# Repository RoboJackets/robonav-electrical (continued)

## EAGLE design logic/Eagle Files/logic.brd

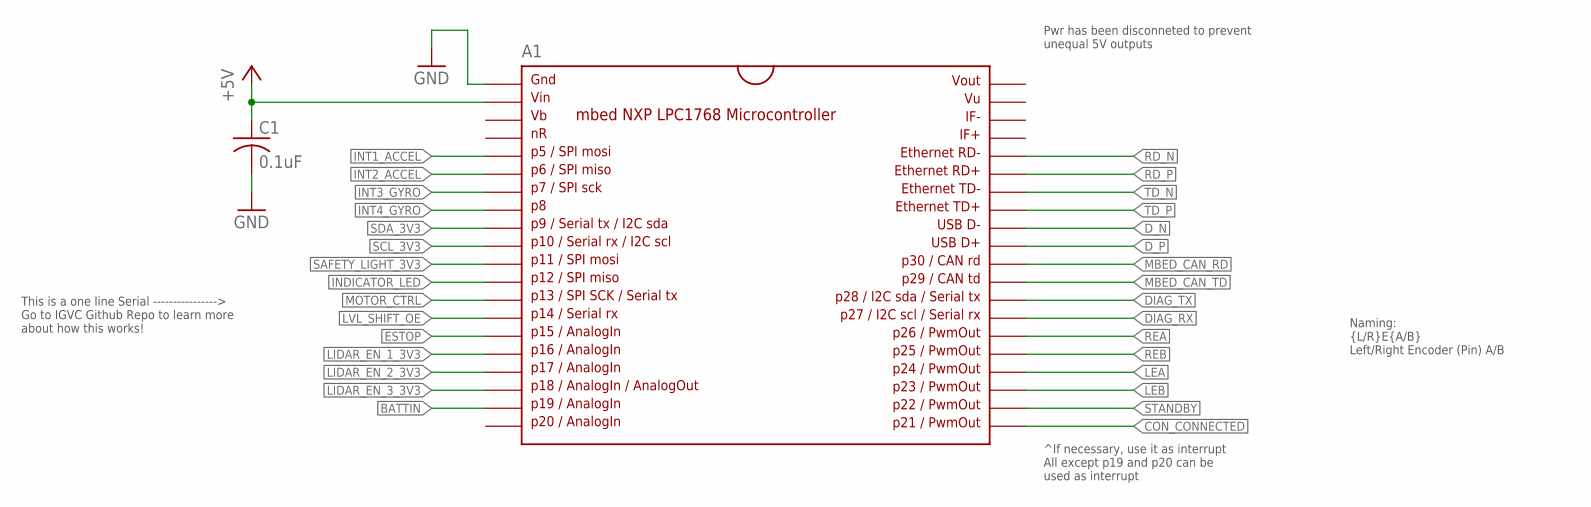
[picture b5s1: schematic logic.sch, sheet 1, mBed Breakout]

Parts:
A1: MBED1768; SPARKFUN-BOARDS_DIL40_0.9
C1: 0.1uF; C0603

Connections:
+5V: A1.2, C1.1; also elsewhere on the board
BATTIN: A1.19; also elsewhere on the board
CON_CONNECTED: A1.21; also elsewhere on the board
DIAG_RX: A1.27; also elsewhere on the board
DIAG_TX: A1.28; also elsewhere on the board
D_N: A1.32; also elsewhere on the board
D_P: A1.31; also elsewhere on the board
ESTOP: A1.15; also elsewhere on the board
GND: A1.1, C1.2; also elsewhere on the board
INDICATOR_LED: A1.12; also elsewhere on the board
INT1_ACCEL: A1.5; also elsewhere on the board
INT2_ACCEL: A1.6; also elsewhere on the board
INT3_GYRO: A1.7; also elsewhere on the board
INT4_GYRO: A1.8; also elsewhere on the board
LEA: A1.24; also elsewhere on the board
LEB: A1.23; also elsewhere on the board
LIDAR_EN_1_3V3: A1.16; also elsewhere on the board
LIDAR_EN_2_3V3: A1.17; also elsewhere on the board
LIDAR_EN_3_3V3: A1.18; also elsewhere on the board
LVL_SHIFT_OE: A1.14; also elsewhere on the board
MBED_CAN_RD: A1.30; also elsewhere on the board
MBED_CAN_TD: A1.29; also elsewhere on the board
MOTOR_CTRL: A1.13; also elsewhere on the board
RD_N: A1.36; also elsewhere on the board
RD_P: A1.35; also elsewhere on the board
REA: A1.26; also elsewhere on the board
REB: A1.25; also elsewhere on the board
SAFETY_LIGHT_3V3: A1.11; also elsewhere on the board
SCL_3V3: A1.10; also elsewhere on the board
SDA_3V3: A1.9; also elsewhere on the board
STANDBY: A1.22; also elsewhere on the board
TD_N: A1.34; also elsewhere on the board
TD_P: A1.33; also elsewhere on the board

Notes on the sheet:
Naming: {L/R}E{A/B} Left/Right Encoder (Pin) A/B
This is a one line Serial ----------------> Go to IGVC Github Repo to learn more about how this works!
^If necessary, use it as interrupt All except p19 and p20 can be used as interrupt
Pwr has been disconneted to prevent unequal 5V outputs

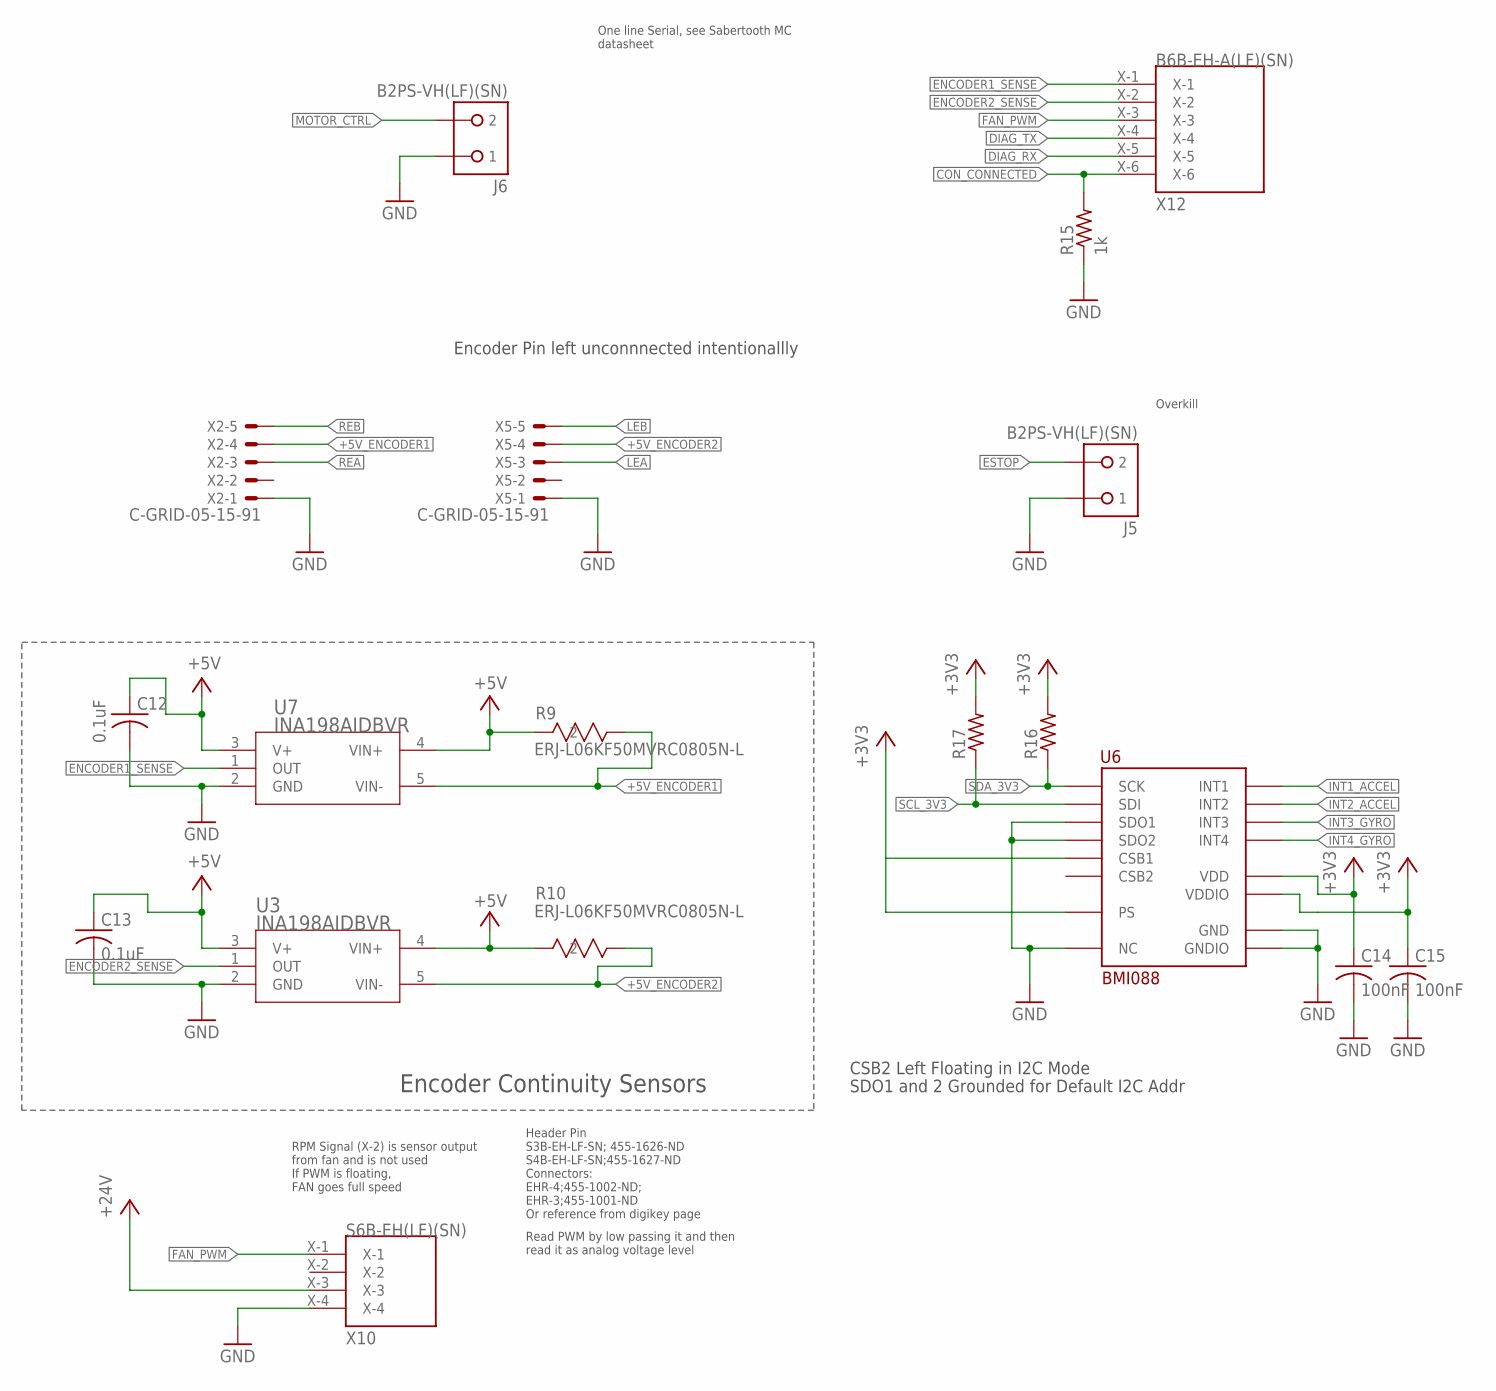
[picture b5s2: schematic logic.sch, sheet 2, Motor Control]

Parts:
C12, C13: 0.1uF; C0603
C14, C15: 100nF; C0603
J5, J6: B2PS-VH(LF)(SN); B2PS-CENTERED
R9, R10: ERJ-L06KF50MVRC0805N-L; RC0805N-L
R15: 1k; R0603
R16, R17: R-US_R0603; R0603
U3, U7: INA198AIDBVR; DBV5
U6: BMI088
X2, X5: C-GRID-05-15-91; 15-91-05
X10: S6B-EH(LF)(SN); S4BEHLFSN
X12: B6B-EH-A(LF)(SN); B6BEHALFSN

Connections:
+3V3: C14.1, C15.1, R16.2, R17.2, U6.P$3 (VDD), U6.P$7 (PS), U6.P$11 (VDDIO); also elsewhere on the board
+5V: C12.1, C13.1, R9.2, R10.2, U3.3 (V+), U3.4 (VIN+), U7.3 (V+), U7.4 (VIN+); also elsewhere on the board
+5V_ENCODER1: R9.1, U7.5 (VIN-), X2.4
+5V_ENCODER2: R10.1, U3.5 (VIN-), X5.4
+24V: X10.X-3; also elsewhere on the board
CON_CONNECTED: R15.2, X12.X-6; also elsewhere on the board
DIAG_RX: X12.X-5; also elsewhere on the board
DIAG_TX: X12.X-4; also elsewhere on the board
ENCODER1_SENSE: U7.1 (OUT), X12.X-1
ENCODER2_SENSE: U3.1 (OUT), X12.X-2
ESTOP: J5.2; also elsewhere on the board
FAN_PWM: X10.X-1, X12.X-3
GND: C12.2, C13.2, C14.2, C15.2, J5.1, J6.1, R15.1, U3.2 (GND), U6.P$2 (NC), U6.P$4 (GND), U6.P$6 (GNDIO), U6.P$10 (SDO2), U6.P$15 (SDO1), U7.2 (GND), X2.1, X5.1, X10.X-4; also elsewhere on the board
INT1_ACCEL: U6.P$16 (INT1); also elsewhere on the board
INT2_ACCEL: U6.P$1 (INT2); also elsewhere on the board
INT3_GYRO: U6.P$12 (INT3); also elsewhere on the board
INT4_GYRO: U6.P$13 (INT4); also elsewhere on the board
LEA: X5.3; also elsewhere on the board
LEB: X5.5; also elsewhere on the board
MOTOR_CTRL: J6.2; also elsewhere on the board
REA: X2.3; also elsewhere on the board
REB: X2.5; also elsewhere on the board
SCL_3V3: R17.1, U6.P$9 (SDI); also elsewhere on the board
SDA_3V3: R16.1, U6.P$8 (SCK); also elsewhere on the board

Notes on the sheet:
Encoder Continuity Sensors
Header Pin S3B-EH-LF-SN; 455-1626-ND S4B-EH-LF-SN;455-1627-ND Connectors: EHR-4;455-1002-ND; EHR-3;455-1001-ND Or reference from digikey page
RPM Signal (X-2) is sensor output from fan and is not used
One line Serial, see Sabertooth MC datasheet
Encoder Pin left unconnnected intentionallly
If PWM is floating, FAN goes full speed
Read PWM by low passing it and then read it as analog voltage level
Overkill
SDO1 and 2 Grounded for Default I2C Addr
CSB2 Left Floating in I2C Mode

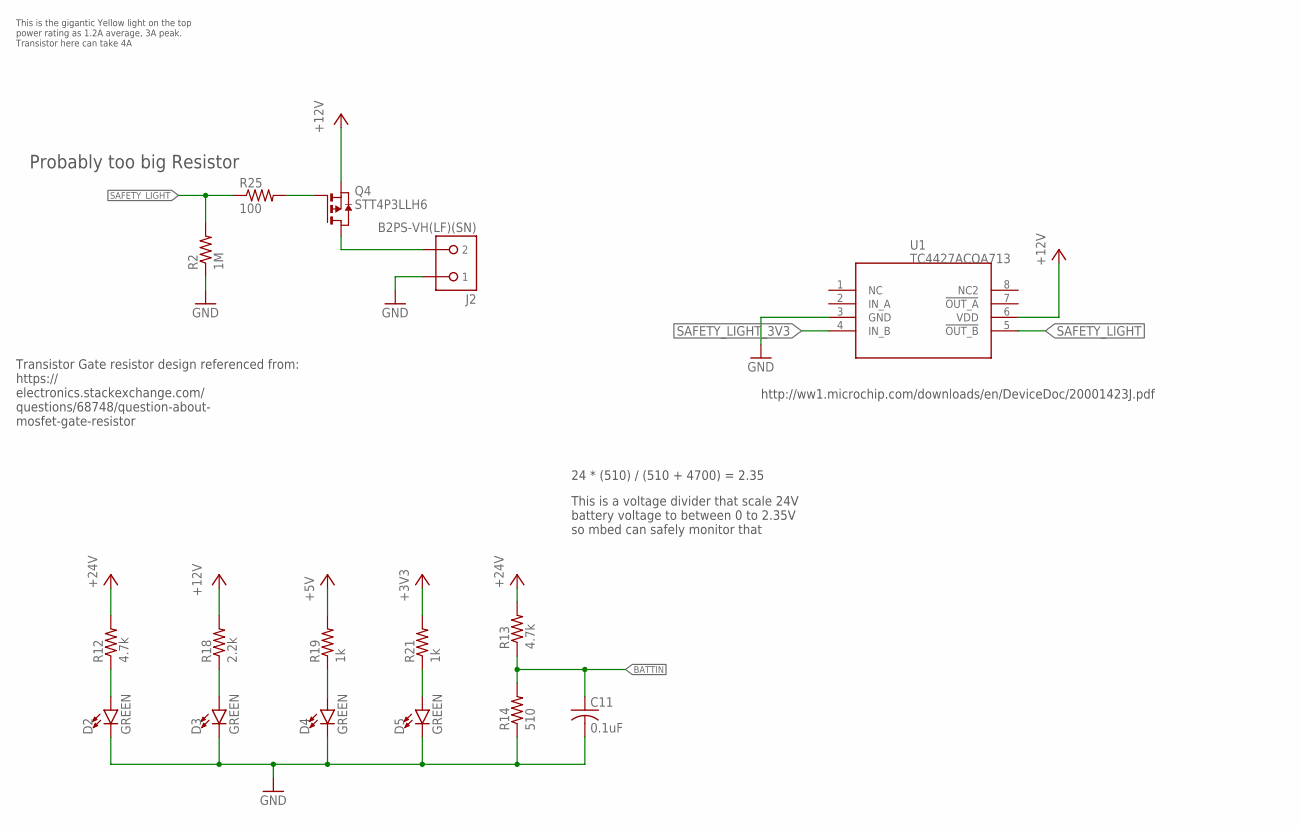
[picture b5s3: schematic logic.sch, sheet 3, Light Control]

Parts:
C11: 0.1uF; C0603
D2, D3, D4, D5: GREEN; LED-0603
J2: B2PS-VH(LF)(SN); B2PS-CENTERED
Q4: STT4P3LLH6; SOT23-6
R2: 1M; R0603
R12, R13: 4.7k; R0603
R14: 510; R0603
R18: 2.2k; R0603
R19, R21: 1k; R0603
R25: 100; R0603
U1: TC4427ACOA713; SOIC-8

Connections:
3V3_LED_R: D5.A, R21.1
5V_LED_R: D4.A, R19.1
12V_LED_R: D3.A, R18.1
+3V3: R21.2; also elsewhere on the board
+5V: R19.2; also elsewhere on the board
+12V: Q4.4 (S), R18.2, U1.6 (VDD); also elsewhere on the board
+24V: R12.2, R13.2; also elsewhere on the board
BATTIN: C11.1, R13.1, R14.2; also elsewhere on the board
GND: C11.2, D2.C, D3.C, D4.C, D5.C, J2.1, R2.1, R14.1, U1.3 (GND); also elsewhere on the board
unnamed: D2.A, R12.1
SAFETY_HRD: J2.2, Q4.1 (D), Q4.2 (D), Q4.5 (D), Q4.6 (D)
SAFETY_LIGHT: R2.2, R25.1, U1.5 (!OUT_B)
SAFETY_LIGHT_3V3: U1.4 (IN_B); also elsewhere on the board
SAFETY_R: Q4.3 (G), R25.2

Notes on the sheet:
This is the gigantic Yellow light on the top power rating as 1.2A average, 3A peak. Transistor here can take 4A
24 * (510) / (510 + 4700) = 2.35
Transistor Gate resistor design referenced from: https:// electronics.stackexchange.com/ questions/68748/question-about- mosfet-gate-resistor
http://ww1.microchip.com/downloads/en/DeviceDoc/20001423J.pdf
Probably too big Resistor
This is a voltage divider that scale 24V battery voltage to between 0 to 2.35V so mbed can safely monitor that

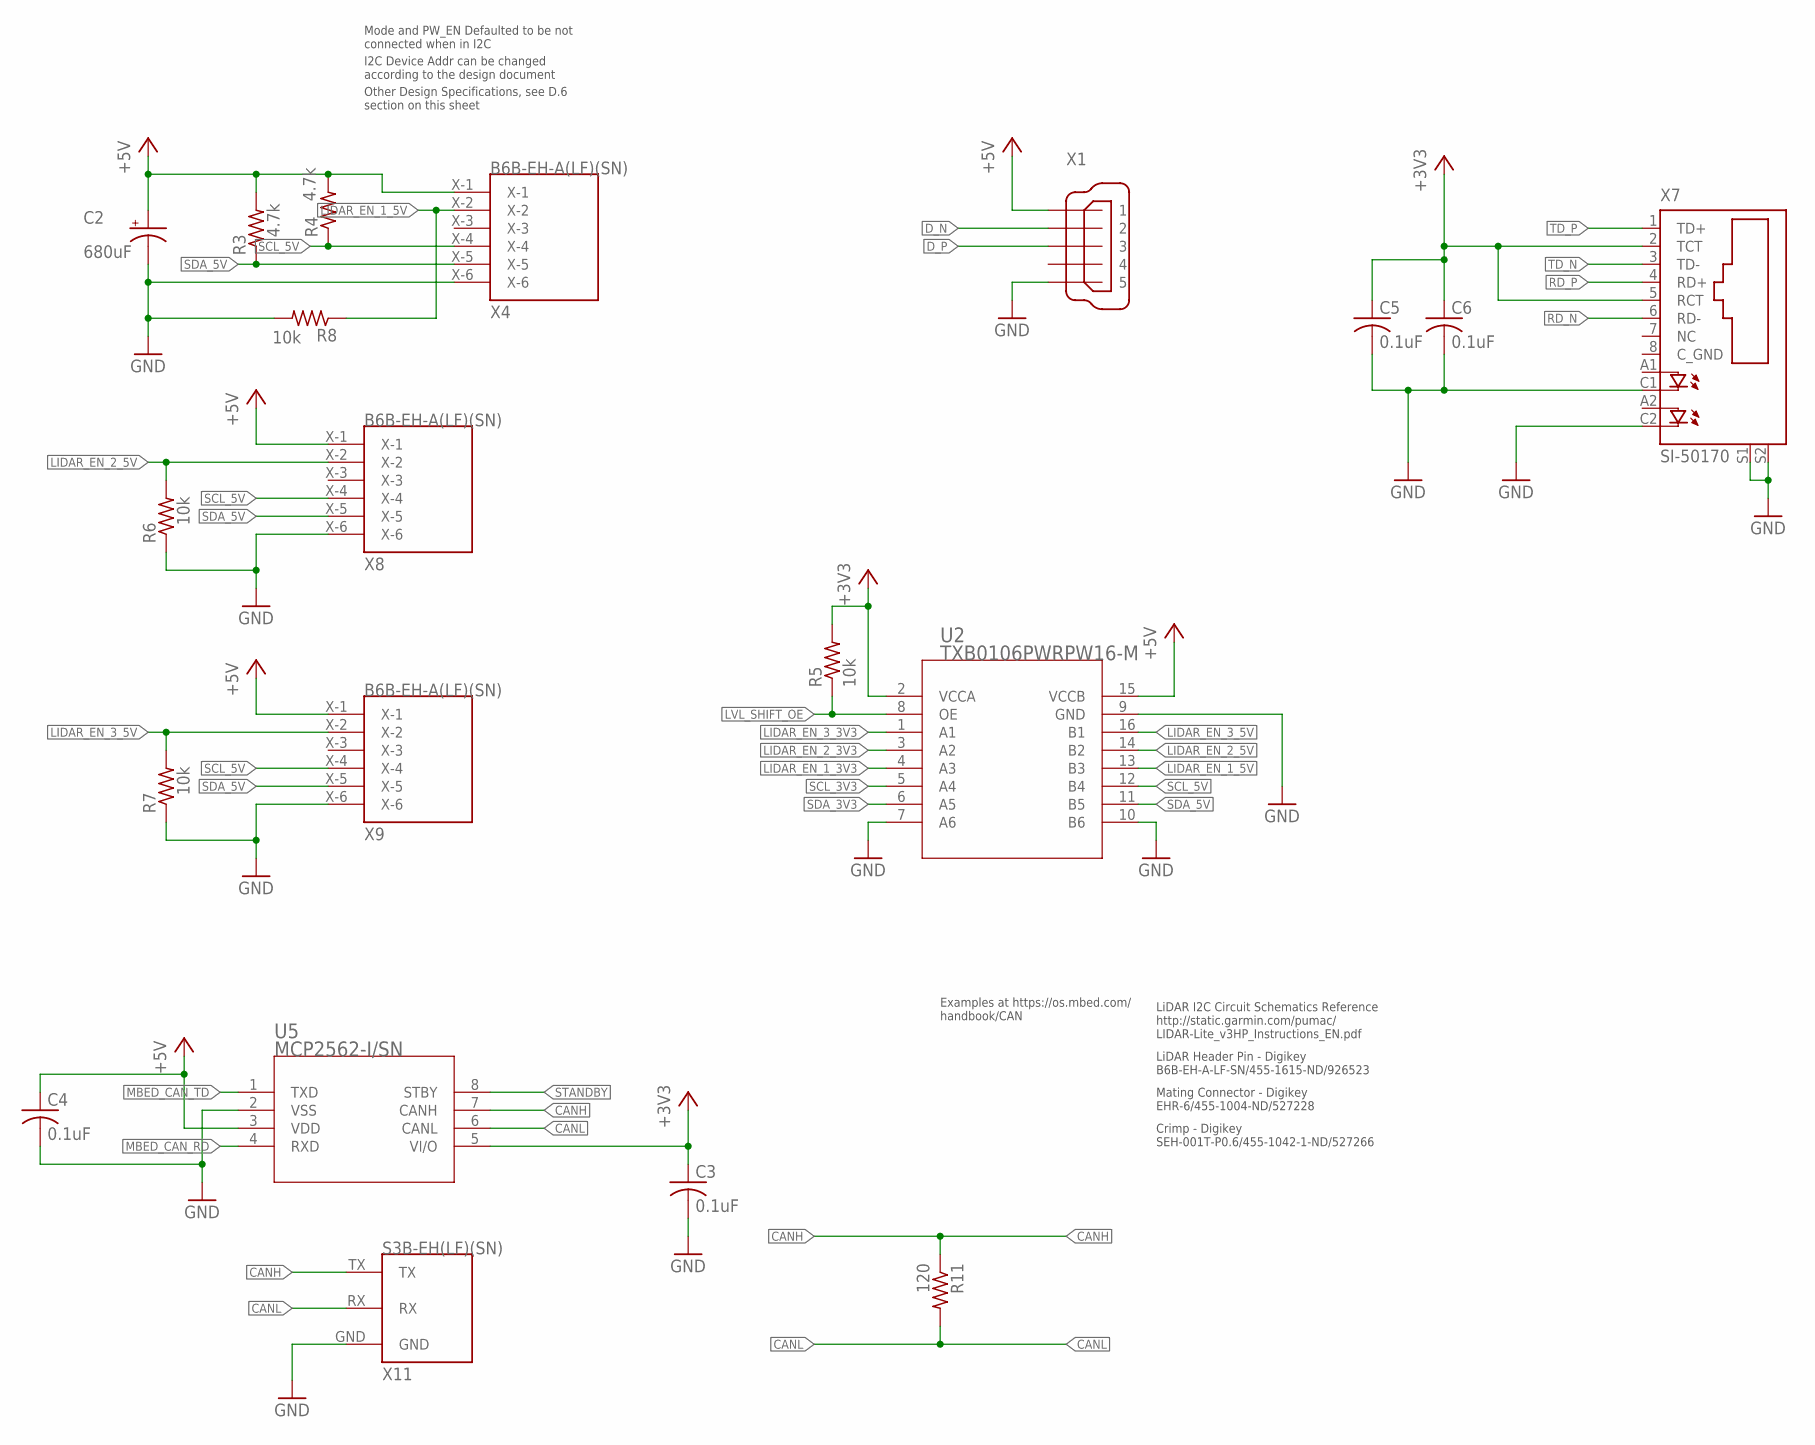
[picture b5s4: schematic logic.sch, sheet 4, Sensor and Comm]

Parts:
C2: 680uF; E5-5
C3, C4, C5, C6: 0.1uF; C0603
R3, R4: 4.7k; R0603
R5, R6, R7, R8: 10k; R0603
R11: 120; R0603
U2: TXB0106PWRPW16-M; PW16-M
U5: MCP2562-I/SN; SOIC8-N_MC
X1: MINI-USB_SHIELD5P4-32005-400; 32005-400
X4, X8, X9: B6B-EH-A(LF)(SN); B6BEHALFSN
X7: SI-50170
X11: S3B-EH(LF)(SN); S3BEHLFSN

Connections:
+3V3: C3.1, C5.1, C6.1, R5.2, U2.2 (VCCA), U5.5 (VI/O), X7.2 (TCT), X7.5 (RCT); also elsewhere on the board
+5V: C2.+, C4.1, R3.2, R4.2, U2.15 (VCCB), U5.3 (VDD), X1.1, X4.X-1, X8.X-1, X9.X-1; also elsewhere on the board
CANH: R11.1, U5.7 (CANH), X11.TX
CANL: R11.2, U5.6 (CANL), X11.RX
D_N: X1.2; also elsewhere on the board
D_P: X1.3; also elsewhere on the board
GND: C2.-, C3.2, C4.2, C5.2, C6.2, R6.1, R7.1, R8.2, U2.7 (A6), U2.9 (GND), U2.10 (B6), U5.2 (VSS), X1.5, X4.X-6, X7.C1 (C), X7.C2 (C1), X7.S1, X7.S2, X8.X-6, X9.X-6, X11.GND; also elsewhere on the board
LIDAR_EN_1_3V3: U2.4 (A3); also elsewhere on the board
LIDAR_EN_1_5V: R8.1, U2.13 (B3), X4.X-2
LIDAR_EN_2_3V3: U2.3 (A2); also elsewhere on the board
LIDAR_EN_2_5V: R6.2, U2.14 (B2), X8.X-2
LIDAR_EN_3_3V3: U2.1 (A1); also elsewhere on the board
LIDAR_EN_3_5V: R7.2, U2.16 (B1), X9.X-2
LVL_SHIFT_OE: R5.1, U2.8 (OE); also elsewhere on the board
MBED_CAN_RD: U5.4 (RXD); also elsewhere on the board
MBED_CAN_TD: U5.1 (TXD); also elsewhere on the board
RD_N: X7.6 (RD-); also elsewhere on the board
RD_P: X7.4 (RD+); also elsewhere on the board
SCL_3V3: U2.5 (A4); also elsewhere on the board
SCL_5V: R4.1, U2.12 (B4), X4.X-4, X8.X-4, X9.X-4
SDA_3V3: U2.6 (A5); also elsewhere on the board
SDA_5V: R3.1, U2.11 (B5), X4.X-5, X8.X-5, X9.X-5
STANDBY: U5.8 (STBY); also elsewhere on the board
TD_N: X7.3 (TD-); also elsewhere on the board
TD_P: X7.1 (TD+); also elsewhere on the board

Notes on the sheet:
LiDAR I2C Circuit Schematics Reference http://static.garmin.com/pumac/ LIDAR-Lite_v3HP_Instructions_EN.pdf
I2C Device Addr can be changed according to the design document
LiDAR Header Pin - Digikey B6B-EH-A-LF-SN/455-1615-ND/926523
Mating Connector - Digikey EHR-6/455-1004-ND/527228
Crimp - Digikey SEH-001T-P0.6/455-1042-1-ND/527266
Mode and PW_EN Defaulted to be not connected when in I2C
Examples at https://os.mbed.com/ handbook/CAN
Other Design Specifications, see D.6 section on this sheet

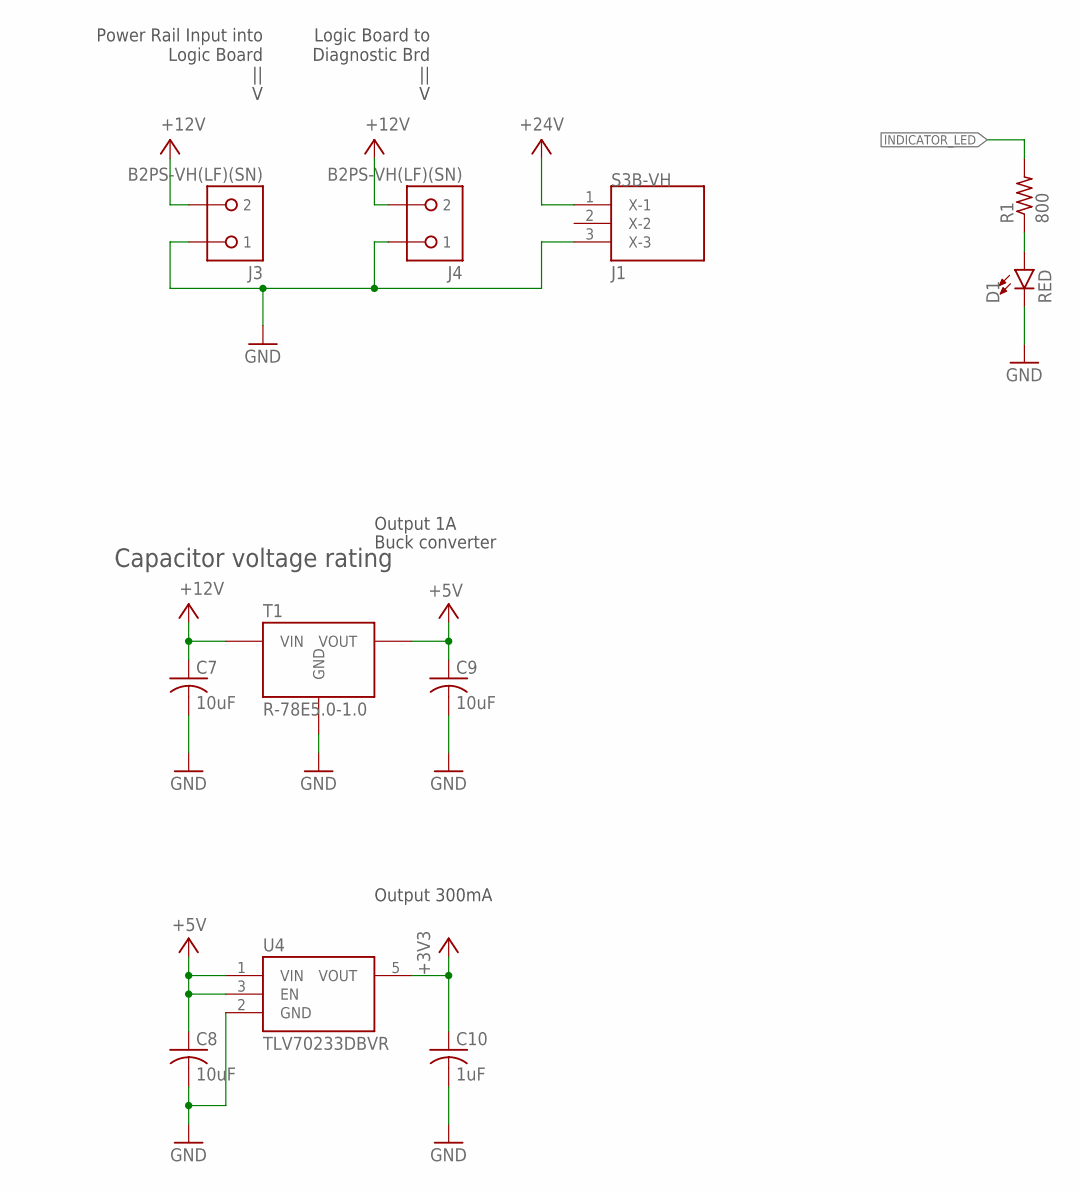
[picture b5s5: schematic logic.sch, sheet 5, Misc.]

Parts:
C7, C8, C9: 10uF; C0805
C10: 1uF; C0805
D1: RED; LED-0603
J1: S3B-VH
J3, J4: B2PS-VH(LF)(SN); B2PS-CENTERED
R1: 800; R0603
T1: R-78E5.0-1.0; R-78E
U4: TLV70233DBVR; SOT-23-5

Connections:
+3V3: C10.1, U4.5 (VOUT); also elsewhere on the board
+5V: C8.1, C9.1, T1.3 (VOUT), U4.1 (VIN), U4.3 (EN); also elsewhere on the board
+12V: C7.1, J3.2, J4.2, T1.1 (VIN); also elsewhere on the board
+24V: J1.1 (X-1); also elsewhere on the board
GND: C7.2, C8.2, C9.2, C10.2, D1.C, J3.1, J4.1, T1.2 (GND), U4.2 (GND); also elsewhere on the board
INDICATOR_LED: R1.2; also elsewhere on the board
unnamed: D1.A, R1.1

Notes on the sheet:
Buck converter
Output 1A
Output 300mA
Power Rail Input into Logic Board || V
Logic Board to Diagnostic Brd || V
Capacitor voltage rating

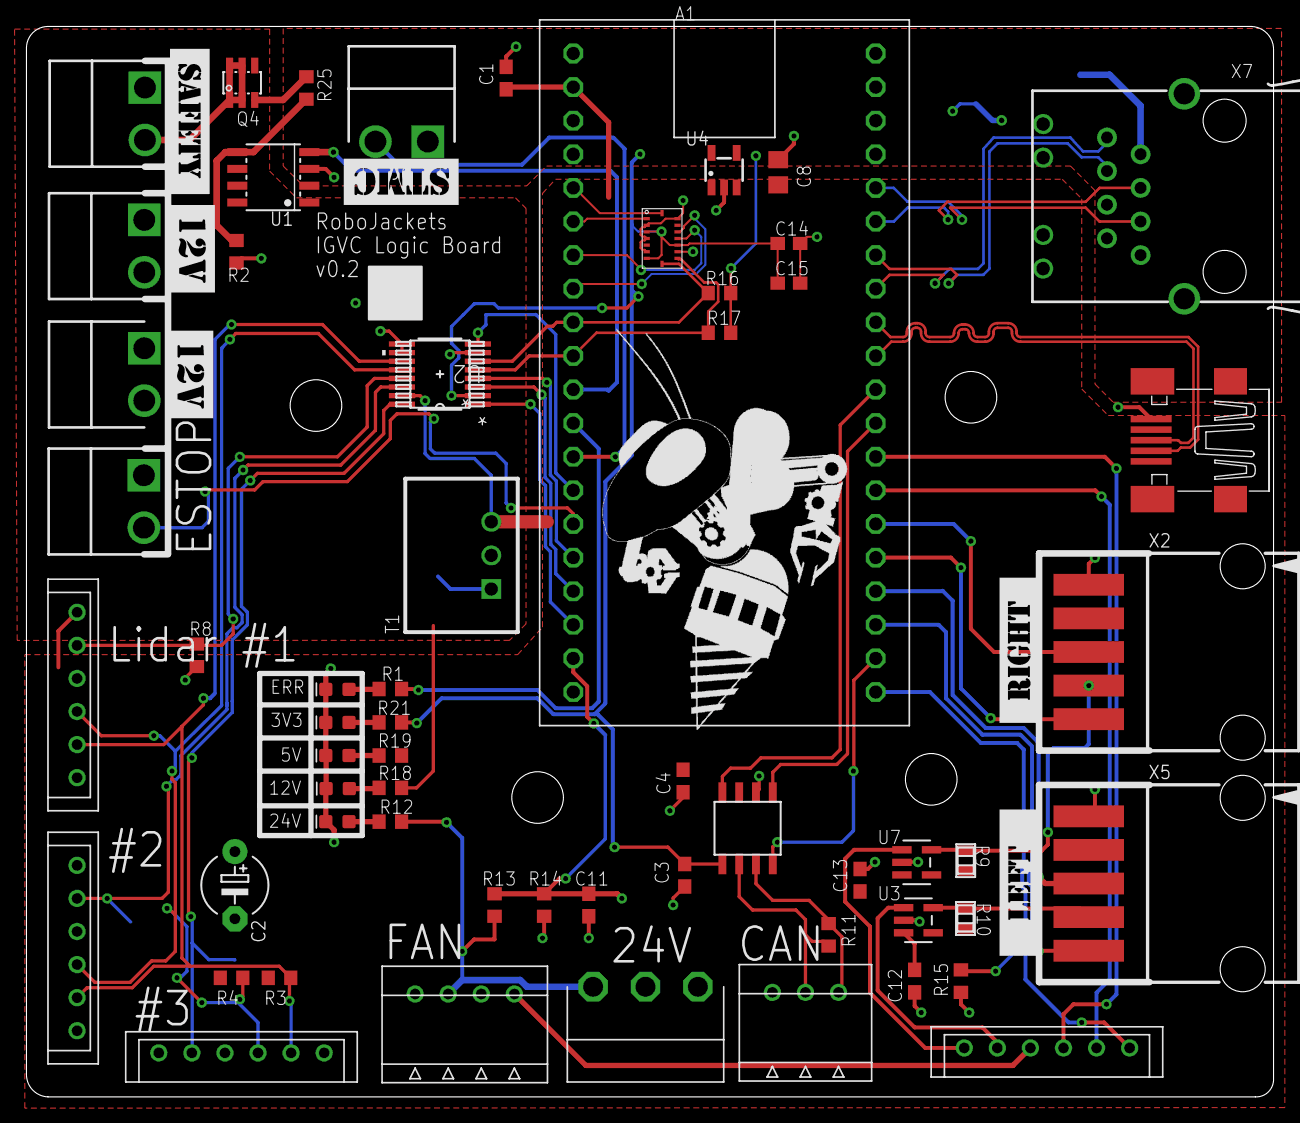
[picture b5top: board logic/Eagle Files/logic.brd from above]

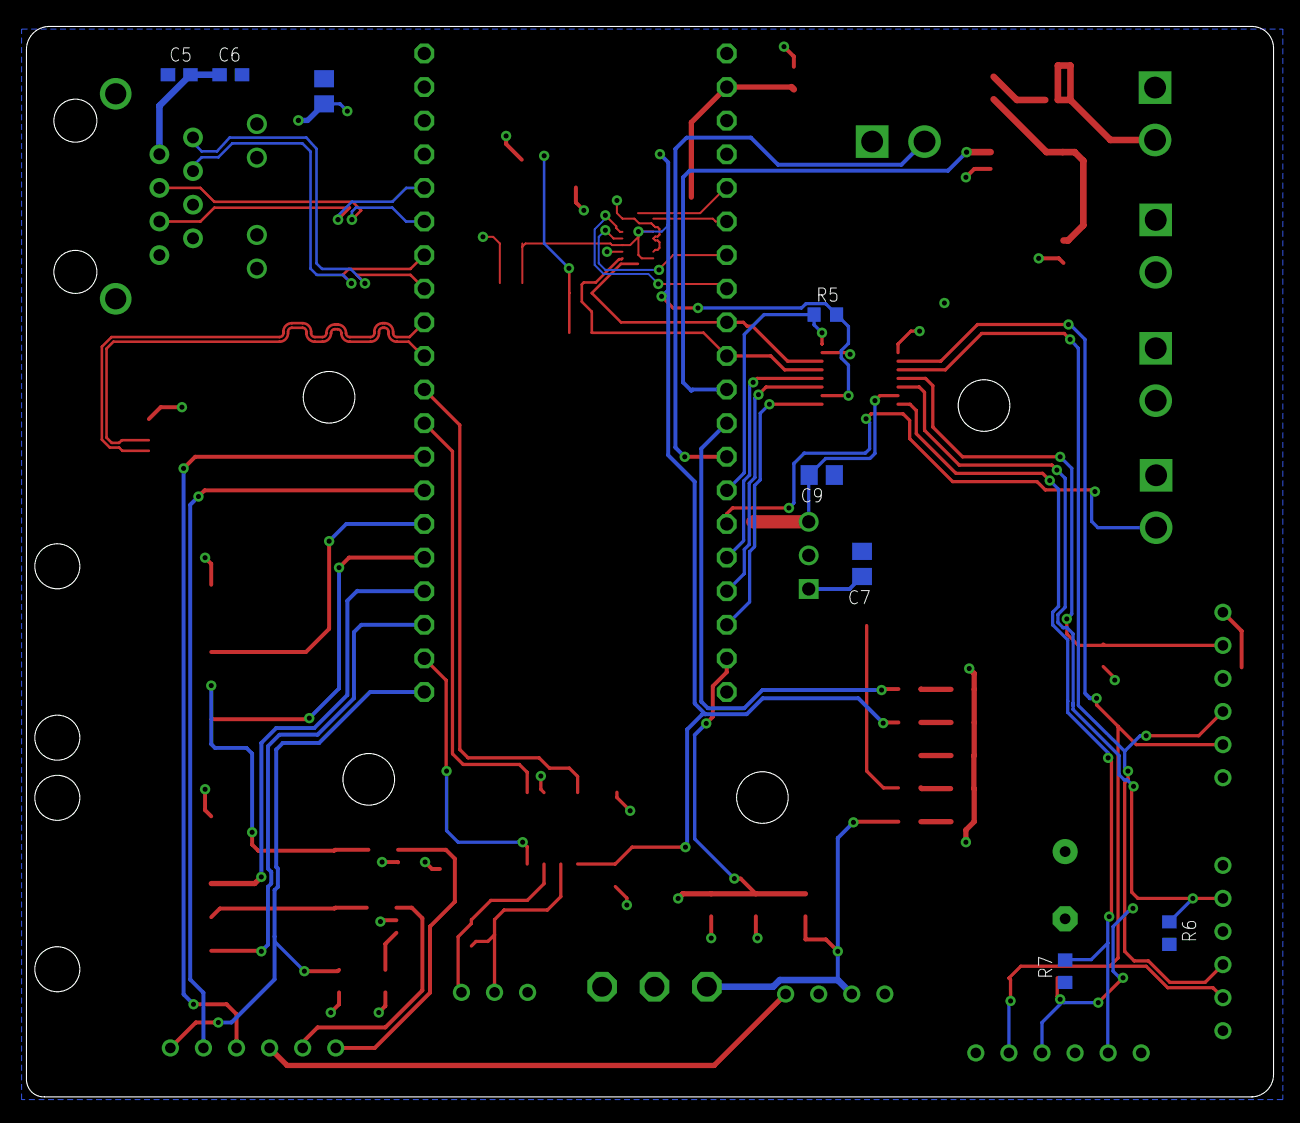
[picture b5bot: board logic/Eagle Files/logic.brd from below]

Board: 2 copper layers, 94.2 x 80.9 mm, 78 parts (8 on the bottom side), 56 nets.

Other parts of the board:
U$1, U$2, U$3, U$4: STANDOFF-HOLE
U$5, U$7: 12V
U$10: ROBOBUZZ_1.4X
U$12: SAFETY
U$13: LEFT
U$14: RIGHT
U$16: STMC

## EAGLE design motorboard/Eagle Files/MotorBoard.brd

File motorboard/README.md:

Instructions to use the Motorboard is included under /Specs\ Sheet Folder

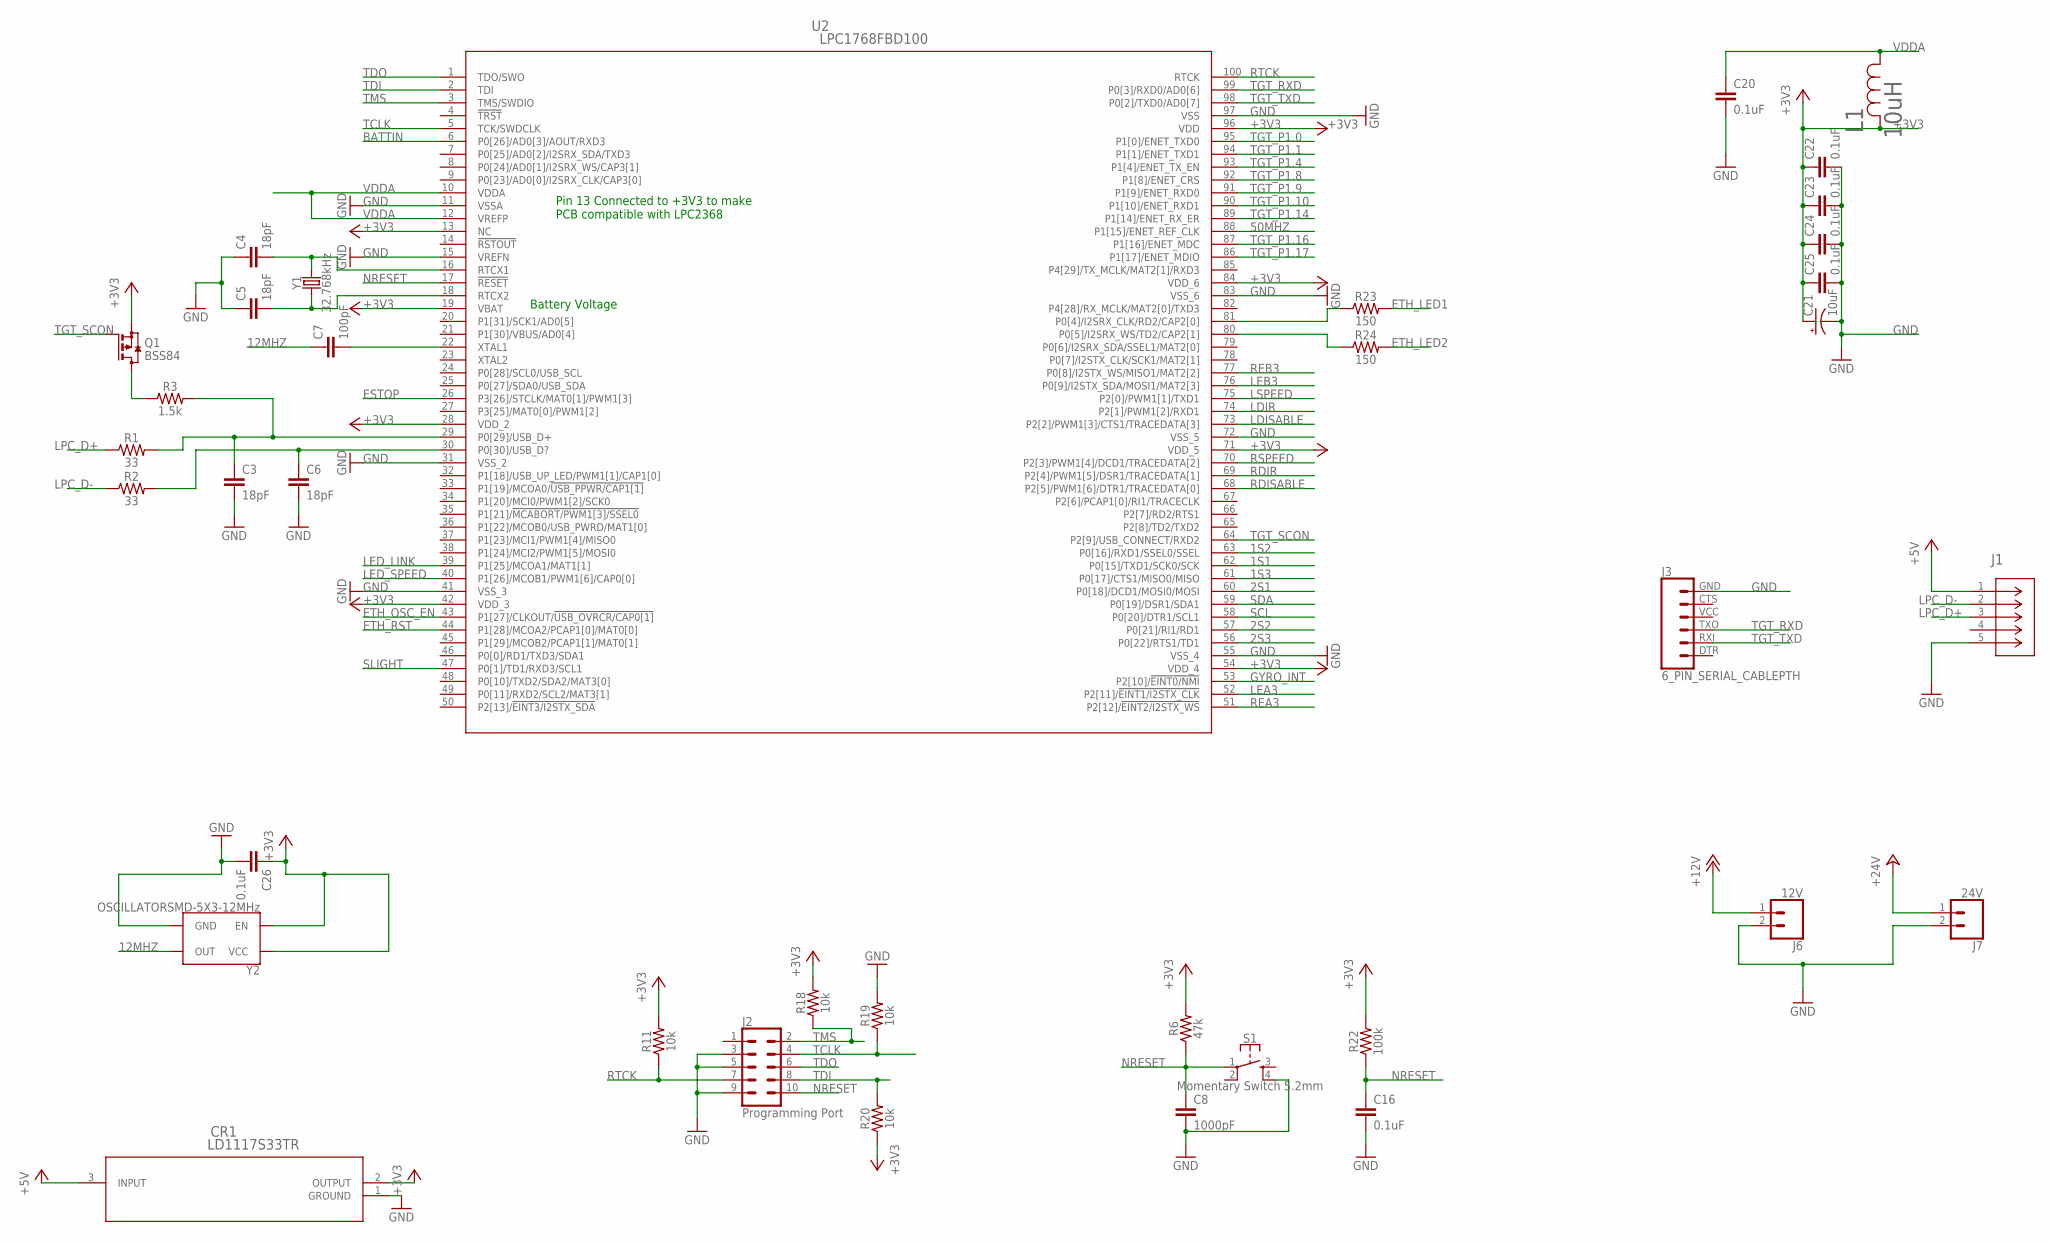
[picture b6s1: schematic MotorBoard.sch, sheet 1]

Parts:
C3, C4, C5, C6: 18pF; 0603
C7: 100pF; 0603
C8: 1000pF; 0603
C16, C20, C22, C23, C24, C25, C26: 0.1uF; 0603
C21: 10uF; 0603-POLAR
CR1: LD1117S33TR; SOT-223
J1: 1981568-1; CONN_1981568-1
J2: Programming Port; 2X5-SHROUDED
J3: 6_PIN_SERIAL_CABLEPTH; FTDI_BASIC
J6: 12V; SCREWTERMINAL-5MM-2
J7: 24V; SCREWTERMINAL-5MM-2
L1: 10uH; IND_1608
Q1: BSS84; SOT23
R1, R2: 33; 0603
R3: 1.5k; 0603
R6: 47k; 0603
R11, R18, R19, R20: 10k; 0603
R22: 100k; 0603
R23, R24: 150; 0603
S1: Momentary Switch 5.2mm; TACTILE_SWITCH_SMD_5.2MM
U2: LPC1768FBD100; SOT407-1
Y1: 32.768kHz; CRYSTAL-SMD-3.2X1.5MM
Y2: OSCILLATORSMD-5X3-12MHz; OSCILLATOR-SMD-5X3.2

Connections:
1S1: U2.62 (P0[15]/TXD1/SCK0/SCK); also elsewhere on the board
1S2: U2.63 (P0[16]/RXD1/SSEL0/SSEL); also elsewhere on the board
1S3: U2.61 (P0[17]/CTS1/MISO0/MISO); also elsewhere on the board
2S1: U2.60 (P0[18]/DCD1/MOSI0/MOSI); also elsewhere on the board
2S2: U2.57 (P0[21]/RI1/RD1); also elsewhere on the board
2S3: U2.56 (P0[22]/RTS1/TD1); also elsewhere on the board
12MHZ: C7.1, Y2.3 (OUT)
50MHZ: U2.88 (P1[15]/ENET_REF_CLK); also elsewhere on the board
+3V3: C21.+, C22.1, C23.1, C24.1, C25.1, C26.1, CR1.2 (OUTPUT), L1.2, Q1.2 (S), R6.2, R11.2, R18.2, R20.1, R22.2, U2.13 (NC), U2.19 (VBAT), U2.28 (VDD_2), U2.42 (VDD_3), U2.54 (VDD_4), U2.71 (VDD_5), U2.84 (VDD_6), U2.96 (VDD), Y2.1 (EN), Y2.4 (VCC); also elsewhere on the board
+5V: CR1.3 (INPUT), J1.1; also elsewhere on the board
+12V: J6.1; also elsewhere on the board
+24V: J7.1; also elsewhere on the board
BATTIN: U2.6 (P0[26]/AD0[3]/AOUT/RXD3); also elsewhere on the board
ESTOP: U2.26 (P3[26]/STCLK/MAT0[1]/PWM1[3]); also elsewhere on the board
ETH_LED1: R23.2; also elsewhere on the board
ETH_LED2: R24.2; also elsewhere on the board
ETH_OSC_EN: U2.43 (P1[27]/CLKOUT/!USB_OVRCR/CAP0[1]); also elsewhere on the board
ETH_RST: U2.44 (P1[28]/MCOA2/PCAP1[0]/MAT0[0]); also elsewhere on the board
GND: C3.2, C4.1, C5.1, C6.2, C8.2, C16.2, C20.2, C21.-, C22.2, C23.2, C24.2, C25.2, C26.2, CR1.1 (GROUND), J1.5, J2.3, J2.5, J2.9, J3.GND (6), J6.2, J7.2, R19.2, S1.4, U2.11 (VSSA), U2.15 (VREFN), U2.31 (VSS_2), U2.41 (VSS_3), U2.55 (VSS_4), U2.72 (VSS_5), U2.83 (VSS_6), U2.97 (VSS), Y2.2 (GND); also elsewhere on the board
GYRO_INT: U2.53 (P2[10]/!EINT0/NMI); also elsewhere on the board
LDIR: U2.74 (P2[1]/PWM1[2]/RXD1); also elsewhere on the board
LDISABLE: U2.73 (P2[2]/PWM1[3]/CTS1/TRACEDATA[3])
LEA3: U2.52 (P2[11]/!EINT1/I2STX_CLK); also elsewhere on the board
LEB3: U2.76 (P0[9]/I2STX_SDA/MOSI1/MAT2[3]); also elsewhere on the board
LED_LINK: U2.39 (P1[25]/MCOA1/MAT1[1]); also elsewhere on the board
LED_SPEED: U2.40 (P1[26]/MCOB1/PWM1[6]/CAP0[0]); also elsewhere on the board
LPC_D+: J1.3, R1.1
LPC_D-: J1.2, R2.1
LSPEED: U2.75 (P2[0]/PWM1[1]/TXD1); also elsewhere on the board
unnamed: C4.2, U2.16 (RTCX1), Y1.P$2 (2)
unnamed: C5.2, U2.18 (RTCX2), Y1.P$1 (1)
unnamed: Q1.3 (D), R3.1
unnamed: C7.2, U2.22 (XTAL1)
unnamed: R23.1, U2.81 (P0[4]/I2SRX_CLK/RD2/CAP2[0])
unnamed: R24.1, U2.80 (P0[5]/I2SRX_WS/TD2/CAP2[1])
NRESET: C8.1, C16.1, J2.10, R6.1, R22.1, S1.1, U2.17 (!RESET)
RDIR: U2.69 (P2[4]/PWM1[5]/DSR1/TRACEDATA[1]); also elsewhere on the board
RDISABLE: U2.68 (P2[5]/PWM1[6]/DTR1/TRACEDATA[0])
REA3: U2.51 (P2[12]/!EINT2/I2STX_WS); also elsewhere on the board
REB3: U2.77 (P0[8]/I2STX_WS/MISO1/MAT2[2]); also elsewhere on the board
RSPEED: U2.70 (P2[3]/PWM1[4]/DCD1/TRACEDATA[2]); also elsewhere on the board
RTCK: J2.7, R11.1, U2.100 (RTCK)
SCL: U2.58 (P0[20]/DTR1/SCL1); also elsewhere on the board
SDA: U2.59 (P0[19]/DSR1/SDA1); also elsewhere on the board
SLIGHT: U2.47 (P0[1]/TD1/RXD3/SCL1); also elsewhere on the board
TCLK: J2.4, R19.1, U2.5 (TCK/SWDCLK)
TDI: J2.8, R20.2, U2.2 (TDI)
TDO: J2.6, U2.1 (TDO/SWO)
TGT_P1.0: U2.95 (P1[0]/ENET_TXD0); also elsewhere on the board
TGT_P1.1: U2.94 (P1[1]/ENET_TXD1); also elsewhere on the board
TGT_P1.4: U2.93 (P1[4]/ENET_TX_EN); also elsewhere on the board
TGT_P1.8: U2.92 (P1[8]/ENET_CRS); also elsewhere on the board
TGT_P1.9: U2.91 (P1[9]/ENET_RXD0); also elsewhere on the board
TGT_P1.10: U2.90 (P1[10]/ENET_RXD1); also elsewhere on the board
TGT_P1.14: U2.89 (P1[14]/ENET_RX_ER); also elsewhere on the board
TGT_P1.16: U2.87 (P1[16]/ENET_MDC); also elsewhere on the board
TGT_P1.17: U2.86 (P1[17]/ENET_MDIO); also elsewhere on the board
TGT_RXD: J3.TXO (3), U2.99 (P0[3]/RXD0/AD0[6])
TGT_SCON: Q1.1 (G), U2.64 (P2[9]/USB_CONNECT/RXD2)
TGT_TXD: J3.RXI (2), U2.98 (P0[2]/TXD0/AD0[7])
TMS: J2.2, R18.1, U2.3 (TMS/SWDIO)
USB_D+: C3.1, R1.2, R3.2, U2.29 (P0[29]/USB_D+)
USB_D-: C6.1, R2.2, U2.30 (P0[30]/USB_D?)
VDDA: C20.1, L1.1, U2.10 (VDDA), U2.12 (VREFP)

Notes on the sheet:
Pin 13 Connected to +3V3 to make PCB compatible with LPC2368
Battery Voltage
